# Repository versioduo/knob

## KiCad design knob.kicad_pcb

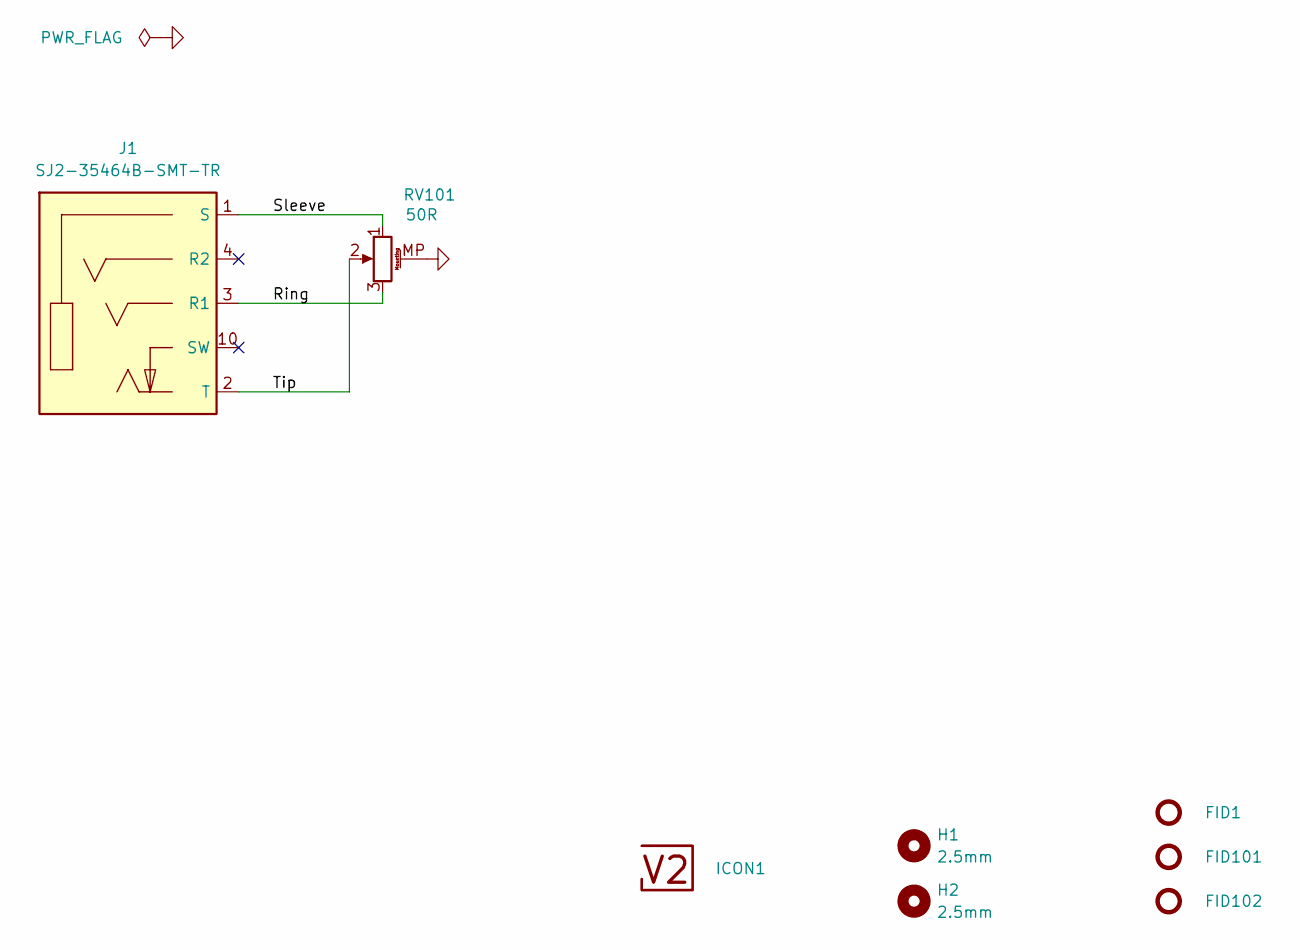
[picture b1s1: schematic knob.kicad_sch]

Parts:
FID1, FID101, FID102: Fiducial_Paste; Fiducial_0.5mm_Mask1mm_Paste
H1, H2: 2.5mm; MountingHole_2.5mm
ICON1: V2-logo; Logo_Small
J1: SJ2-35464B-SMT-TR; CUI_SJ2-35464B-SMT-TR; Mouser 490-SJ2-35464BSMT-TR
RV101: 50R; ALPS-RK1191114001

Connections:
/Ring: J1.3 (R1), RV101.3
/Sleeve: J1.1 (S), RV101.1
/Tip: J1.2 (T), RV101.2
GND: RV101.MP (MountPin)

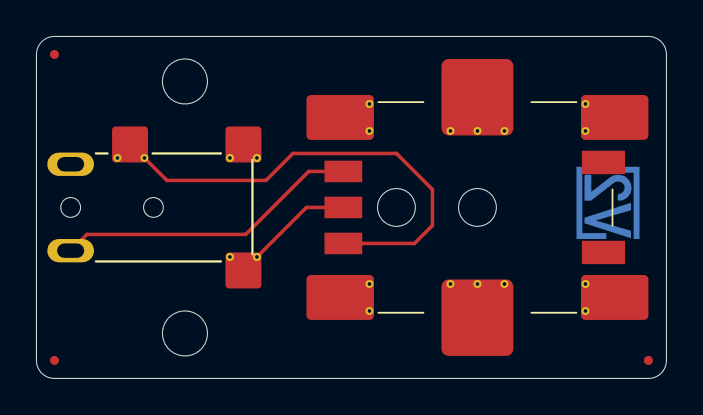
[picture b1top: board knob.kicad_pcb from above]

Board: 2 copper layers, 35.0 x 19.0 mm, 8 parts (1 on the bottom side), 3 nets.

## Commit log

2025-12-29 Import
2026-02-15 Update Library
